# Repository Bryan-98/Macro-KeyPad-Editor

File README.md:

# Macro KeyPad Editor

Using my custom tkinter python program you will be able to change the rgb leds, change each keys macro and choose an audio program. This program is buitl around the arduino pro micro with the atmega32u4 microprocessor.

## Custom Macro Keypad
This program is used to control a custom keypad based around an arduino pro micro 5V/16MHz.

GitHub Repo: [Check out my project](https://github.com/Bryan-98/audio-macro-keypad)

### Complete Build

### Board Render

## Compatible MicroControllers
[SparkFun](https://www.sparkfun.com/pro-micro-5v-16mhz.html): Pro Micro - 5V/16MHz

##
 
Shield: [![CC BY-NC-SA 4.0][cc-by-nc-sa-shield]][cc-by-nc-sa]

This work is licensed under a
[Creative Commons Attribution-NonCommercial-ShareAlike 4.0 International License][cc-by-nc-sa].

[![CC BY-NC-SA 4.0][cc-by-nc-sa-image]][cc-by-nc-sa]

[cc-by-nc-sa]: http://creativecommons.org/licenses/by-nc-sa/4.0/
[cc-by-nc-sa-image]: https://licensebuttons.net/l/by-nc-sa/4.0/88x31.png
[cc-by-nc-sa-shield]: https://img.shields.io/badge/License-CC%20BY--NC--SA%204.0-lightgrey.svg

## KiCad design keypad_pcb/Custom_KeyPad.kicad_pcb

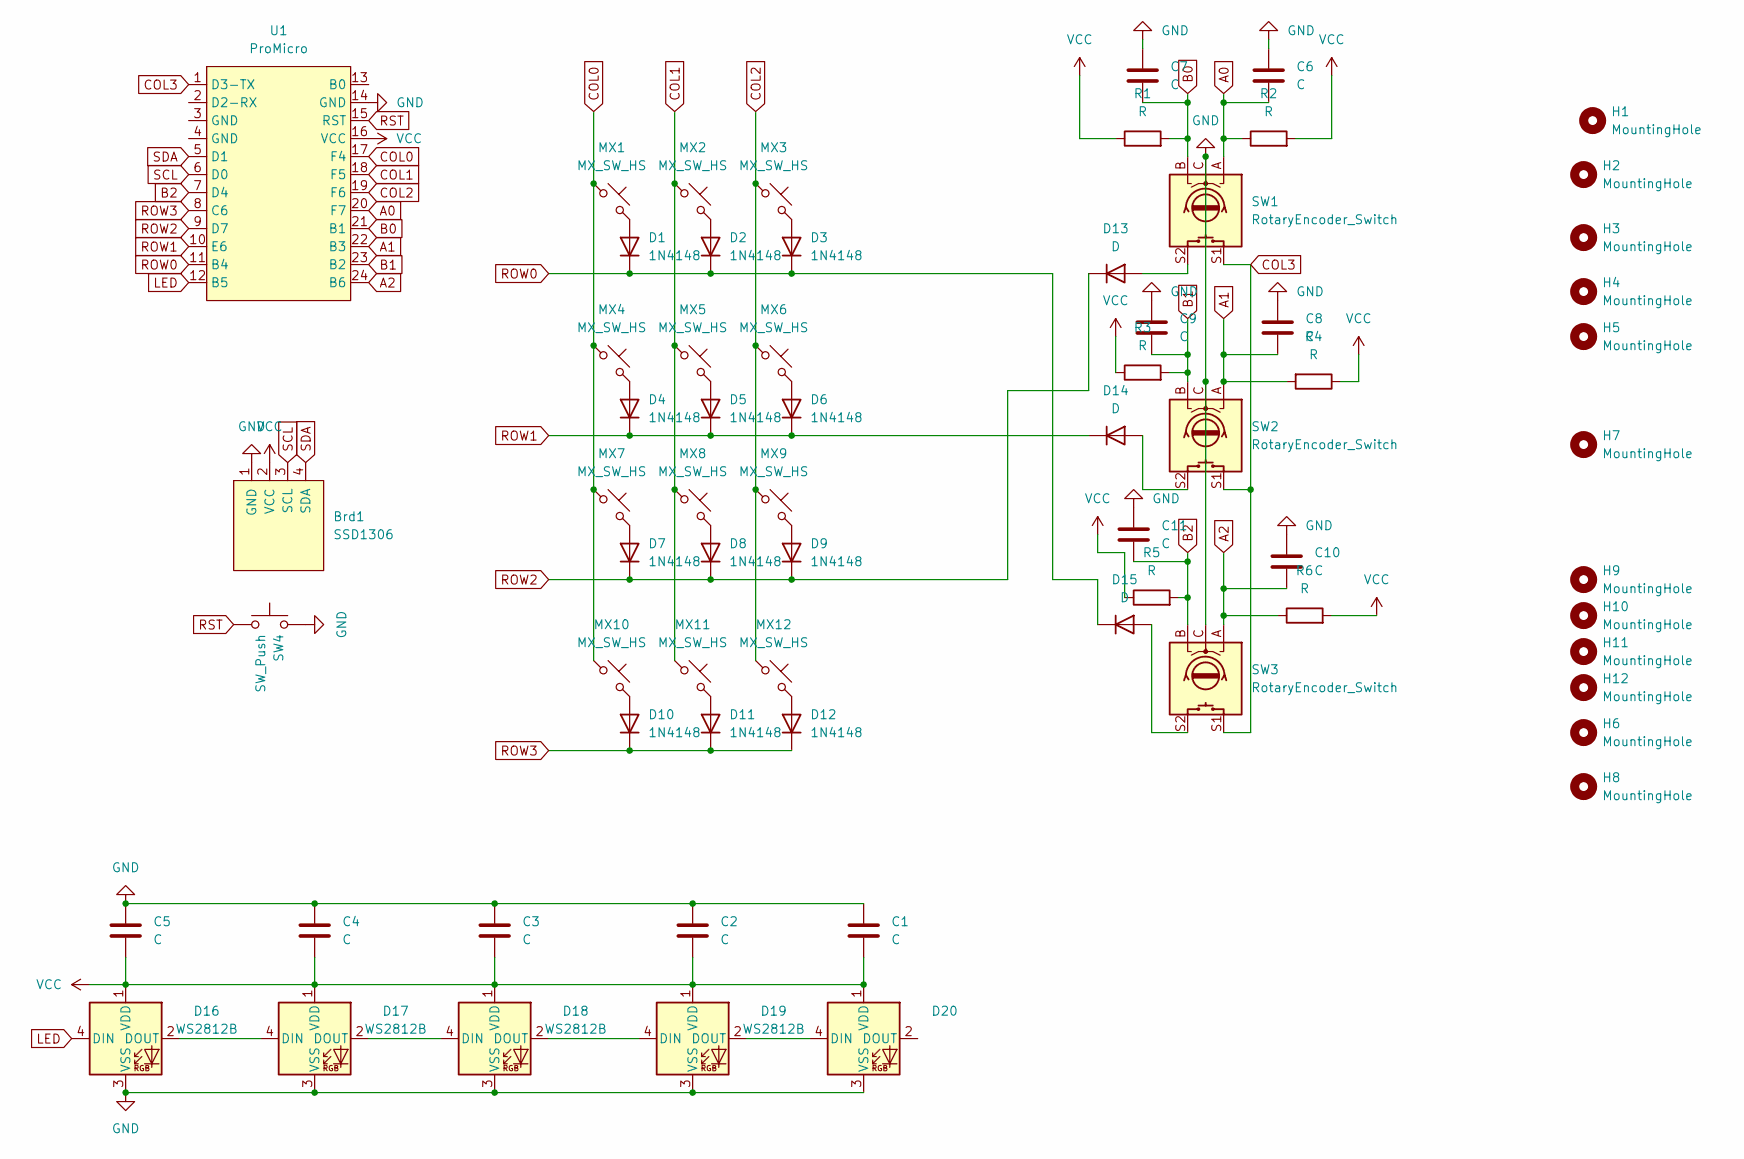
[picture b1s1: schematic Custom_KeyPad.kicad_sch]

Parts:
Brd1: SSD1306; 128x64OLED
C1, C2, C3, C4, C5, C6, C7, C8, C9, C10, C11: C; C_0603_1608Metric_Pad1.08x0.95mm_HandSolder
D1, D2, D3, D4, D5, D6, D7, D8, D9, D10, D11, D12: 1N4148; D_DO-35_SOD27_P7.62mm_Horizontal
D13, D14, D15: D; D_DO-35_SOD27_P7.62mm_Horizontal
D16, D17, D18, D19, D20: WS2812B; LED_WS2812B_PLCC4_5.0x5.0mm_P3.2mm
H1, H2, H3, H4, H5, H6, H7, H8, H9, H10, H11, H12: MountingHole; MountingHole_2.2mm_M2_ISO7380_Pad_TopBottom
MX1, MX2, MX3, MX4, MX5, MX6, MX7, MX8, MX9, MX10, MX11, MX12: MX_SW_HS; SW_MX_HS_1u
R1, R2, R3, R4, R5, R6: R; R_0805_2012Metric_Pad1.20x1.40mm_HandSolder
SW1, SW2, SW3: RotaryEncoder_Switch; RotaryEncoder_Alps_EC11E-Switch_Vertical_H20mm
SW4: SW_Push; SW_Push_SPST_NO_Alps_SKRK
U1: ProMicro; ProMicro_USBup

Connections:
A0: C6.1, R2.1, SW1.A, U1.20 (F7)
A1: C8.2, R4.2, SW2.A, U1.22 (B3)
A2: C10.1, R6.1, SW3.A, U1.24 (B6)
B0: C7.1, R1.2, SW1.B, U1.21 (B1)
B1: C9.1, R3.2, SW2.B, U1.23 (B2)
B2: C11.1, R5.2, SW3.B, U1.7 (D4)
COL0: MX1.1, MX4.1, MX7.1, MX10.1, U1.17 (F4)
COL1: MX2.1, MX5.1, MX8.1, MX11.1, U1.18 (F5)
COL2: MX3.1, MX6.1, MX9.1, MX12.1, U1.19 (F6)
COL3: SW1.S1, SW2.S1, SW3.S1, U1.1 (D3-TX)
GND: Brd1.1 (GND), C1.2, C2.2, C3.2, C4.2, C5.2, C6.2, C7.2, C8.1, C9.2, C10.2, C11.2, D16.3 (VSS), D17.3 (VSS), D18.3 (VSS), D19.3 (VSS), D20.3 (VSS), SW1.C, SW2.C, SW3.C, SW4.2, U1.14 (GND)
LED: D16.4 (DIN), U1.12 (B5)
unnamed: D1.2 (A), MX1.2
unnamed: D2.2 (A), MX2.2
unnamed: D3.2 (A), MX3.2
unnamed: D4.2 (A), MX4.2
unnamed: D5.2 (A), MX5.2
unnamed: D6.2 (A), MX6.2
unnamed: D7.2 (A), MX7.2
unnamed: D8.2 (A), MX8.2
unnamed: D9.2 (A), MX9.2
unnamed: D10.2 (A), MX10.2
unnamed: D11.2 (A), MX11.2
unnamed: D12.2 (A), MX12.2
unnamed: D13.2 (A), SW1.S2
unnamed: D14.2 (A), SW2.S2
unnamed: D15.2 (A), SW3.S2
unnamed: D16.2 (DOUT), D17.4 (DIN)
unnamed: D17.2 (DOUT), D18.4 (DIN)
unnamed: D18.2 (DOUT), D19.4 (DIN)
unnamed: D19.2 (DOUT), D20.4 (DIN)
ROW0: D1.1 (K), D2.1 (K), D3.1 (K), D15.1 (K), U1.11 (B4)
ROW1: D4.1 (K), D5.1 (K), D6.1 (K), D14.1 (K), U1.10 (E6)
ROW2: D7.1 (K), D8.1 (K), D9.1 (K), D13.1 (K), U1.9 (D7)
ROW3: D10.1 (K), D11.1 (K), D12.1 (K), U1.8 (C6)
RST: SW4.1, U1.15 (RST)
SCL: Brd1.3 (SCL), U1.6 (D0)
SDA: Brd1.4 (SDA), U1.5 (D1)
VCC: Brd1.2 (VCC), C1.1, C2.1, C3.1, C4.1, C5.1, D16.1 (VDD), D17.1 (VDD), D18.1 (VDD), D19.1 (VDD), D20.1 (VDD), R1.1, R2.2, R3.1, R4.1, R5.1, R6.2, U1.16 (VCC)

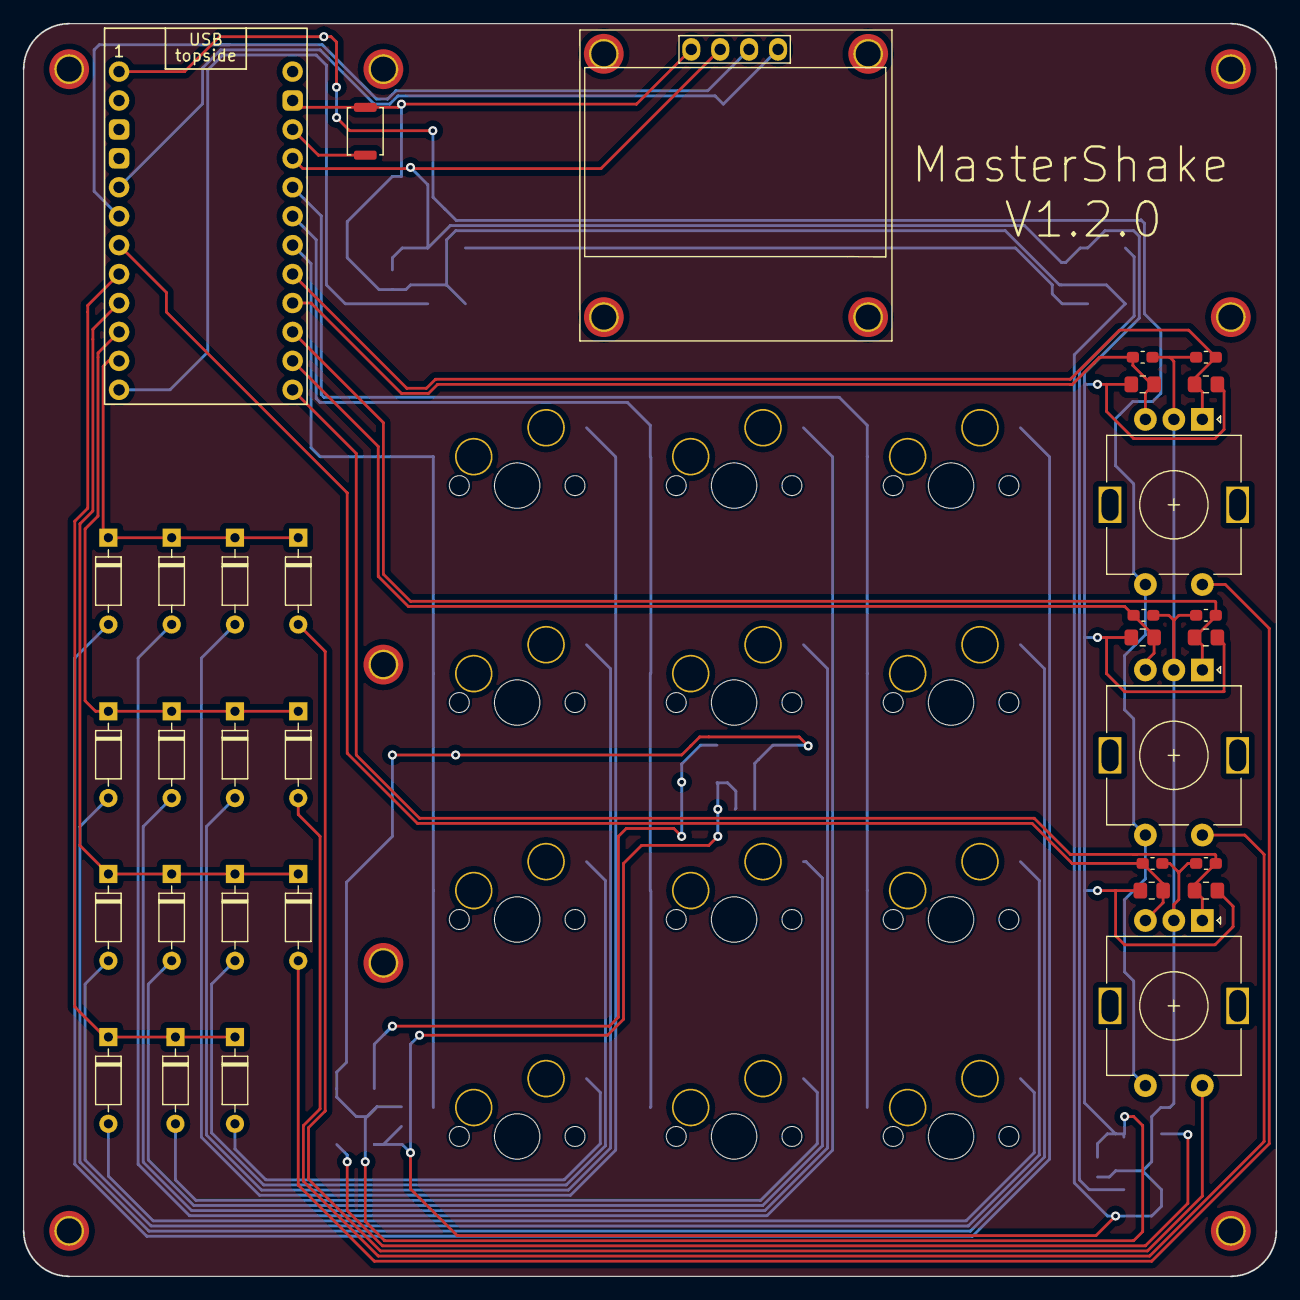
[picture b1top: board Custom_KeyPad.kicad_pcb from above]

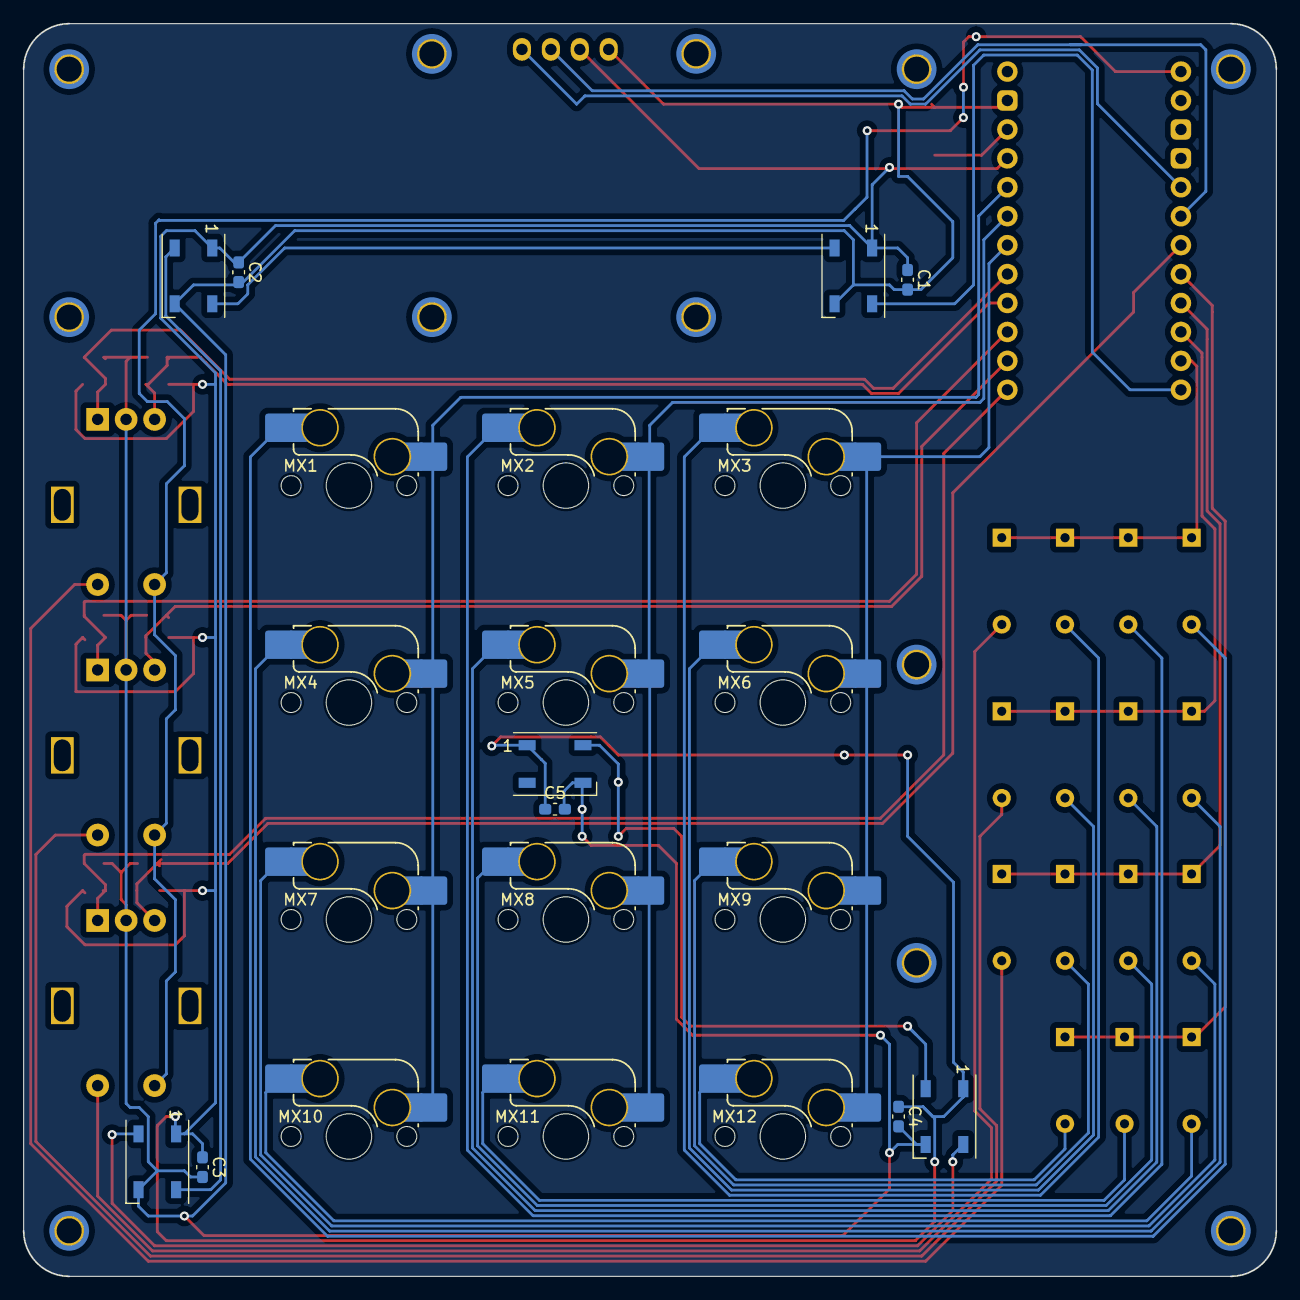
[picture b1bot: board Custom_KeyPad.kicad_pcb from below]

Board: 2 copper layers, 110.0 x 110.0 mm, 67 parts (22 on the bottom side), 39 nets.

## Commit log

2023-12-13 First Upload
2024-03-05 1.0V
    First production push.
2024-03-06 Removed files
2024-04-14 Removed arduino ino files.
2024-05-14 Icon change
    renamed icon file name.
2025-07-14 Bug Fixes
    - Fixed macro keys not saving correctly. Macros was creating a new set of list when saving to the json file.
    - Macro name carries over when editing.
2025-07-21 Key Function Update
    - Rewrote key function to use Frame objects
    - Working on adding individual rgb led for each key
2025-07-28 UX Redesign
    - Reworking on the UX.
    - Button matrix is now resizable.
    - Working on device verification.
2025-08-16 Dynamic Window
    * Added function to adjust window size to accommodate different board sizes.
    * Added function to to read macro pad info such as size, number of leds, if encoders or installed, version and name of device.
2025-08-20 Maintenance
    * Code clean up
    * Added error handling
